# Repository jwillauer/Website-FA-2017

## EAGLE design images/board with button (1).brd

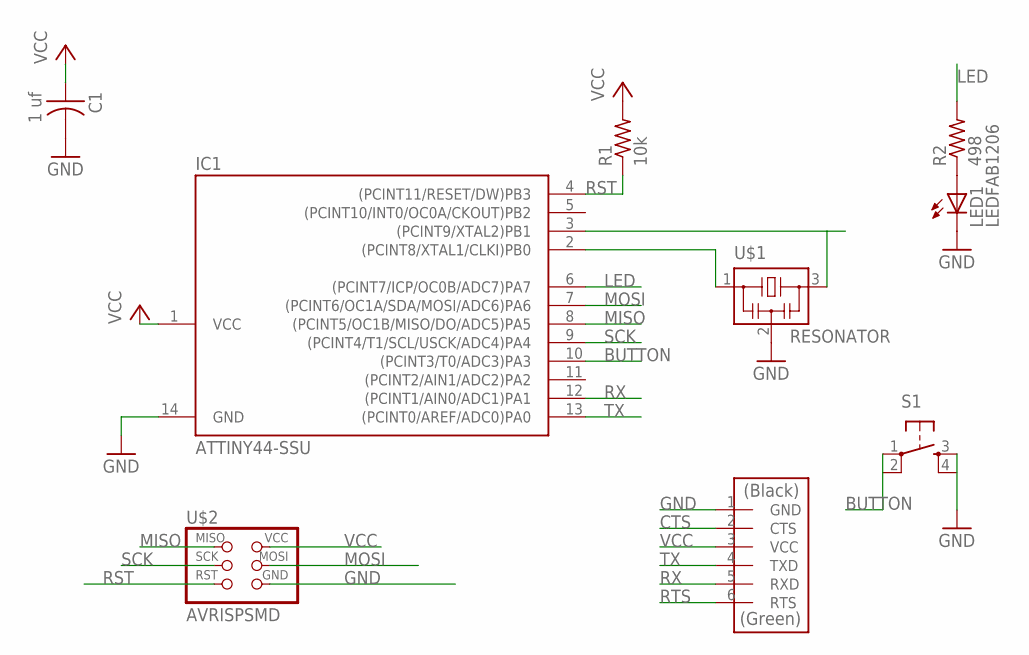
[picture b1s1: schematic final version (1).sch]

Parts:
C1: 1 uf; C1206FAB
IC1: ATTINY44-SSU; SOIC14
LED1: LEDFAB1206; LED1206FAB
R1: 10k; R1206FAB
R2: 498; R1206FAB
S1: 6MM_SWITCH6MM_SWITCH; 6MM_SWITCH
U$1: RESONATOR; EFOBM
U$2: AVRISPSMD; 2X03SMD
U$3: FTDI-SMD-HEADER; 1X06SMD

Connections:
BUTTON: IC1.10 ((PCINT3/T0/ADC3)PA3), S1.1
CTS: U$3.2 (CTS)
GND: C1.2, IC1.14 (GND), LED1.2 (C), S1.3 (S), U$1.2, U$2.6 (GND), U$3.1 (GND)
LED: IC1.6 ((PCINT7/ICP/OC0B/ADC7)PA7), R2.2
MISO: IC1.8 ((PCINT5/OC1B/MISO/DO/ADC5)PA5), U$2.1 (MISO)
MOSI: IC1.7 ((PCINT6/OC1A/SDA/MOSI/ADC6)PA6), U$2.4 (MOSI)
unnamed: IC1.2 ((PCINT8/XTAL1/CLKI)PB0), U$1.1
unnamed: LED1.1 (A), R2.1
unnamed: IC1.3 ((PCINT9/XTAL2)PB1), U$1.3
RST: IC1.4 ((PCINT11/RESET/DW)PB3), R1.1, U$2.5 (RST)
RTS: U$3.6 (RTS)
RX: IC1.12 ((PCINT1/AIN0/ADC1)PA1), U$3.5 (RXD)
SCK: IC1.9 ((PCINT4/T1/SCL/USCK/ADC4)PA4), U$2.3 (SCK)
TX: IC1.13 ((PCINT0/AREF/ADC0)PA0), U$3.4 (TXD)
VCC: C1.1, IC1.1 (VCC), R1.2, U$2.2 (VCC), U$3.3 (VCC)

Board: 2 copper layers, 9 parts (0 on the bottom side), 13 nets, no tracks yet.

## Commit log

2019-12-11 2
    2
2020-02-05 addition
